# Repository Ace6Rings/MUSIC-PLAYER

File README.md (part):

# NOIR MUSIC PLAYER

# Why?

Why did I build something like this? Well, I am sick and tired of buying spotify premium every month. I looked for mp3 players online but nearly all of them have the same flaw(s). 
They either have a very short battery life or they don't support bluetooth. This would mean that my headphones will last three times as long as a typical mp3 player. So, I solved all of these problems with my own music player.

# Features

  - expandable storage via micro sd card
  - bluetooth range of ~100 meters in open air
  - Dual compatibility with both wired and wireless. 
  - High quality wired and wireless audio
  - Extremely high battery life (not tested)

## Electronics

So what about my electronics makes these features possible?

I use the NRF5430 <br>
  - The NRF5430 is a dual core chip that have the capability of being hyper efficient during its operation. <br>
  - Its power consumption is measured in the microamps during sleep mode and miliamps during full operation.

The PCM5102A and the TPA6132A2RTE <br>
  - the audio from common microcontrollers are low quality and unenjoyable for music. So I used the PCM5102A. It is a high quality DAC which will be wired to the TPA6132ARTE. <br>
  - the TPA6132ARTE increases the volume of the sound and also helps with the bass.<br>
  - with these two components, the wired quality should be no different (if not, better) than a phone or a typical mp3 player.

What about some safety features?

I have 2 layers of protection.

  According to my schematic, the battery and the usbc is tied to the same net. This means that they share the same electrical path.<br>
  To prevent any damage, I used mosfets which prevents both of them from turning on at the same time.<br>
  Additionally, I used the PRTR5V0U2X. It is a tvs diode which can prevent damage to the usbc and the board if something goes horribly wrong.

The rest of the electronics can be found in the electronics subdirectory. You can also find the production files there too. For the reviewer, make sure to read the mini readme in the electronics directory.

## Mechanical

The case of the music player is largely modeled after the Iphone 16 pro's dimensions. It is a reasonable size for a mp3 player and is also the reason why I can fit such a big battery.

There isn't any special about the case itself. This is designed for printers like the A1 mini, A1, and X1 Carbon with PLA basic.
If you took a look at my CAD already, you might be worried about how thin the wall is at the micro sd slot. So I ran some simulations.

I put a force of 20 newtons onto the faces of the socket and made the opposite wall a fixed support.
There could be more things you might want to see. You can do that under MECHANICAL and then click on simulations. <br>
NOTE: you need both the workbench file and also the zipped file too
CONTROL

This is the "before" part of the simulation.

And this is the after. 

Pretty much the same right? this means that my design is sound and could be used (as long as the user isn't a brute)

## Code
### MAKE SURE TO READ THE CORRESPONDING README INCLUDED IN THE CODE DIRECTORY TO ACTUALLY BUILD IT.
The backend of the code is built entirely by NORDIC, the company behind the NRF chips. I used their existing audio code so that I don't need to code my own (they have tens of thousands of lines of code)

The gui and function is limited because I have not recieved my pcb yet, and won't know what will happen if i implement something more than audio playback and some config files. This will change once I get my pcb.

Also note that the vast majority of the code is by NORDIC and their open source templates. All I did was make config files.

# Process

So what exactly is under the hood? Its a big schematic, so there is going to be 3 images.

## Schematic

As you can see, I'm using the NRF 5340 to power this project. Is there really much to say about this as of right now? Not really.

In this image, we can see that I'm using the TPA and PCM. These components work together to make wired audio great (hopefully). On the user side, you don't have to worry about this.
There is a headphone jack, and that is where you're going to plug in your headphones.

(yeah i don't know what to say about the schematic, I guess its cool?)

## PCB

If you've already opened the PCB file, then you might've been confused or bamboozled by how messy it is. But it really isn't!

This is what it is supposed to look like without user drawings (i used them to align things but never deleted them so I remember how much pain I went through).

Everything that needed to be said is already said in the features subtitle, but as an addendum, I added a cool snowman.

# How to use
Well how do you use it? I don't really know to be honest. The code is rudimentary and will be improved upon when I get my parts. As of right now, the controls are simple. The four buttons indicate direction, the center button indicates selection, and the rotary encoder is for volume up down and also a faster way to navigate the (future) gui.

# How to build

If you want to know how to build this physically, then heres a simple guide.

Thankfully, you don't need to do much at all! (assuming your pcb is already assembled. If not, good luck)

Just follow the steps in order!

1.Grab a soldering iron to put heat set inserts into the hole that label 1 is indicating. This is OPTIONAL, but you will need to adjust the cad to make it 2mm instead of 3mm.<br>
2.Screw in the screws as indicated in Label 1. There is only two holes but four mounts. Make sure to orientate it correctly! (the ports should line up with the case)<br>
3.Put the battery inside the two walls as indicated in label 2. Since everyone's printers are different, you will likely have to sand it. You can put double sided tape or velcro to secure the battery further, but otherwise, it should be fine. <br>
4.Put the ANO encoder into the cutout as indicated in Label 4.<br>
5.Put the cover onto the ANO encoder as indicated in Label 5.<br>
6.Screw it both in as indicated in Label 6.<br>
6.Use the JST compatible wires and connect them to the PCB.<br>
7.Do the same thing you just did to the ANO encoder in step 3. Instead, this time, you'll apply the same principle to the screen in Label 7, 8, and 9.<br>
NOTE: If you are unconfident in your soldering abilities, especially for the screen, you may adjust the "leeway" variable under "screen" folder and then the "mount" subfolder. The default is 2mm, do not go past 2.1mm. You may lower it if you want to, but the default should be ok. In addition, it is not reccomended to use the included pin headers for the screen, just solder the wire directly. The cover will hide any cosmetic issues.<br>

Hey! What about the battery? <br>
Well, since everyone can choose what lipo battery they will be using, I decided to make the battery area an open space. All you have to do is take a small piece of double sided tape (which many other commericial products do!) and tape the battery to the case. 

# BOM

NOTE: This file might be confusing. So heres some clarifications <br>

  - QTY refers to the actual amount needed. Amount refers to the amount bought due to minimum purchase limits. For assortment kits, qty is just 1.
  - Any item below the 45th row is not needed for this project (well they are). They are misc items that I don't have and I must put it down to get funding.
  - The NRF 5340 DK dev board is not needed, you only need a pico or etc to serve as an external programmer. I need this because I need to debug my code after I recieve my parts (so yes, again, this is for funding purposes)
  - shipping is done weirdly because I don't know how else to do it. However, you don't have to worry about that. There is a number on a seemingly random item that tells you the shipping price. Since alot of these items come from the same shop, the shipping is counted once. So items only have a shipping fee if it is the first on the list (by row) to have that specific shop.

And additionally, you might be thinking "woah, why is this so expensive?!" <br>
Well, most of the cost is actually the tools I need to program and assemble my project. You might already have these items!<br>

[tableConvert.com_6tsmnr.md](https://github.com/user-attachments/files/29273329/tableConvert.com_6tsmnr.md)
| Reference                                                                                 | Qty | Item                                                                                                          | DNP | Exclude from BOM | Exclude from Board  | Footprint                                                             | Datasheet                                                                                                                               | Link                                                                                                                                                                                                                                                                                                                                                                                                                                                                                                                                                                                                                                                                           | Amount | Cost  | SUBTOTAL | SHIPPING | TAXES     | TOTAL      |
|-------------------------------------------------------------------------------------------|-----|---------------------------------------------------------------------------------------------------------------|-----|------------------|---------------------|-----------------------------------------------------------------------|-----------------------------------------------------------------------------------------------------------------------------------------|--------------------------------------------------------------------------------------------------------------------------------------------------------------------------------------------------------------------------------------------------------------------------------------------------------------------------------------------------------------------------------------------------------------------------------------------------------------------------------------------------------------------------------------------------------------------------------------------------------------------------------------------------------------------------------|--------|-------|----------|----------|-----------|------------|
| C1,C4,C8,C10,C12,C24,C39,C40,C41,C43,C44,C45,C46,C50,C53                                  | 15  | 1u                                                                                                            |     |                  |                     | Capacitor_SMD:C_0402_1005Metric                                       |                                                                                                                                         | https://www.lcsc.com/product-detail/C29266.html?s_z=n_q_t_1uf%25200402&spm=wm.fly.bg.0.xh___wm.ssy.tc.0.tz&lcsc_vid=RFJeBVYFQQVeBV1XQwIMBQVQRlAPVVZeFlJcU1wHRwcxVlNeRlVXVF1VR1RaXjsOAxUeFF5JWBYZEEoKFBINSQcJGk4%3D                                                                                                                                                                                                                                                                                                                                                                                                                                                             | 100    | 0.53  | 209.2    | 7.27     | 21.724225 | 266.504225 |
| C2, C26, C47                                                                              | 3   | 2.2u                                                                                                          |     |                  |                     | Capacitor_SMD:C_0402_1005Metric                                       |                                                                                                                                         | https://www.lcsc.com/product-detail/C170151.html?s_z=n_q_t_2.2uf%25200402&spm=wm.fly.bg.0.xh___wm.ssy.tc.0.tz&lcsc_vid=RFJeBVYFQQVeBV1XQwIMBQVQRlAPVVZeFlJcU1wHRwcxVlNeRlVXVF1RRFNZXjsOAxUeFF5JWBYZEEoKFBINSQcJGk4NBhADEA4cHktXRlVcSQwSGg0%3D                                                                                                                                                                                                                                                                                                                                                                                                                                  | 50     | 0.5   |          |          |           |            |
| C3,C7,C15,C16,C17,C18,C19,C20,C21,C22,C23,C28,C29,C30,C31,C32,C33,C36,C38,C42,C48,C51,C52 | 23  | 100n                                                                                                          |     |                  |                     | Capacitor_SMD:C_0402_1005Metric                                       |                                                                                                                                         | https://www.lcsc.com/product-detail/C1525.html?s_z=n_q_t_100%2520nf%25200402&spm=wm.fly.bg.0.xh___wm.ssy.tc.0.tz&lcsc_vid=RFJeBVYFQQVeBV1XQwIMBQVQRlAPVVZeFlJcU1wHRwcxVlNeRlVXU1RQRlVbVjsOAxUeFF5JWBYZEEoKFBINSQcJGk4NBhADEA4cHktXRlVcSQwSGg0%3D                                                                                                                                                                                                                                                                                                                                                                                                                               | 100    | 0.23  |          |          |           |            |
| C5                                                                                        | 1   | 4.7u                                                                                                          | DNP |                  | Excluded from board | Capacitor_SMD:C_0603_1608Metric                                       |                                                                                                                                         |                                                                                                                                                                                                                                                                                                                                                                                                                                                                                                                                                                                                                                                                                |        |       |          |          |           |            |
| C6,C9,C11,C27                                                                             | 4   | 4.7u                                                                                                          |     |                  |                     | Capacitor_SMD:C_0603_1608Metric                                       |                                                                                                                                         | https://www.lcsc.com/product-detail/C19666.html?s_z=n_q_t_4.7uf&spm=wm.fly.bg.0.xh___wm.ssy.tc.1.tz&lcsc_vid=RFJeBVYFQQVeBV1XQwIMBQVQRlAPVVZeFlJcU1wHRwcxVlNeRlVXU1VSR1FWVTsOAxUeFF5JWBYZEEoKFBINSQcJGk4dAgUUFAk%3D                                                                                                                                                                                                                                                                                                                                                                                                                                                            | 10     | 0.22  |          |          |           |            |
| C13                                                                                       | 1   | 2.2n                                                                                                          |     |                  |                     | Capacitor_SMD:C_0402_1005Metric                                       |                                                                                                                                         | https://www.lcsc.com/product-detail/C107082.html?s_z=n_q_t_2.2nf&spm=wm.fly.bg.0.xh___wm.ssy.tc.0.tz&lcsc_vid=RFJeBVYFQQVeBV1XQwIMBQVQRlAPVVZeFlJcU1wHRwcxVlNeRlVXU1VfQlNWVDsOAxUeFF5JWBYZEEoKFBINSQcJGk4NBhADEA4cHktXRlVcSQwSGg0%3D                                                                                                                                                                                                                                                                                                                                                                                                                                           | 100    | 0.42  |          |          |           |            |
| C14                                                                                       | 1   | 0.7p                                                                                                          |     |                  |                     | Capacitor_SMD:C_0402_1005Metric                                       |                                                                                                                                         | https://www.lcsc.com/product-detail/C161349.html?s_z=n_q_t_0.7pf&spm=wm.fly.bg.0.xh___wm.ssy.tc.0.tz&lcsc_vid=RFJeBVYFQQVeBV1XQwIMBQVQRlAPVVZeFlJcU1wHRwcxVlNeRlVXU1ZSQFRaXzsOAxUeFF5JWBYZEEoKFBINSQcJGk4dAgUUFAk%3D                                                                                                                                                                                                                                                                                                                                                                                                                                                           | 50     | 0.83  |          |          |           |            |
| C37,C49                                                                                   | 2   | 10u                                                                                                           |     |                  |                     | Capacitor_SMD:C_0603_1608Metric                                       |                                                                                                                                         | https://www.lcsc.com/product-detail/C96446.html?s_z=n_q_t_10%2520uf&spm=wm.fly.bg.1.xh___wm.ssy.tc.1.tz&lcsc_vid=RFJeBVYFQQVeBV1XQwIMBQVQRlAPVVZeFlJcU1wHRwcxVlNeRlVXU1BRTlhbVTsOAxUeFF5JWBYZEEoKFBINSQcJGk4NBhADEA4cHktXRlVcSQwSGg0%3D                                                                                                                                                                                                                                                                                                                                                                                                                                        | 20     | 1.07  |          |          |           |            |
| C54                                                                                       | 1   | 10n                                                                                                           |     |                  |                     | Capacitor_SMD:C_0402_1005Metric                                       |                                                                                                                                         | https://www.lcsc.com/product-detail/C15195.html?s_z=n_q_t_10%2520nf&spm=wm.fly.bg.1.xh___wm.ssy.tc.0.tz&lcsc_vid=RFJeBVYFQQVeBV1XQwIMBQVQRlAPVVZeFlJcU1wHRwcxVlNeRlVXU1NST1BdVjsOAxUeFF5JWBYZEEoKFBINSQcJGk4NBhADEA4cHktXRlVcSQwSGg0%3D                                                                                                                                                                                                                                                                                                                                                                                                                                        | 100    | 0.25  |          |          |           |            |
| C55                                                                                       | 1   | NC                                                                                                            | DNP |                  |                     | Capacitor_SMD:C_0402_1005Metric                                       |                                                                                                                                         |                                                                                                                                                                                                                                                                                                                                                                                                                                                                                                                                                                                                                                                                                |        |       |          |          |           |            |
| D1, D3                                                                                    | 2   | POWER                                                                                                         |     |                  |                     | LED_SMD:LED_0603_1608Metric                                           |                                                                                                                                         | https://www.lcsc.com/product-detail/C19171394.html?s_z=n_q_t_led%25200603&spm=wm.fly.bg.0.xh___wm.ssy.tc.0.tz&lcsc_vid=RFJeBVYFQQVeBV1XQwIMBQVQRlAPVVZeFlJcU1wHRwcxVlNeRlVXU1xWQ1FYVzsOAxUeFF5JWBYZEEoKFBINSQcJGk4NBhADEA4cHktXRlVcSQwSGg0%3D                                                                                                                                                                                                                                                                                                                                                                                                                                  | 100    | 0.58  |          |          |           |            |
| D2                                                                                        | 1   | PRTR5V0U2X                                                                                                    |     |                  |                     | Package_TO_SOT_SMD:SOT-143                                            | https://assets.nexperia.com/documents/data-sheet/PRTR5V0U2X.pdf                                                                         | https://www.lcsc.com/product-detail/C2827688.html?s_z=n_q_PRTR5V0U2X&spm=wm.fly.bg.3.xh&lcsc_vid=RFJeBVYFQQVeBV1XQwIMBQVQRlAPVVZeFlJcU1wHRwcxVlNeRlVXUlRRT1JWVzsOAxUeFF5JWBYZEEoKFBINSQcJGk4eFQsCAgIaSgADAwAHC0slRlhfUFVVTlVADxALGw%3D%3D                                                                                                                                                                                                                                                                                                                                                                                                                                      | 10     | 0.61  |          |          |           |            |
| E1                                                                                        | 1   | 2450AT43B100E                                                                                                 |     |                  |                     | MyFootprintLibrary:ANTENNA_2450AT43B100E                              |                                                                                                                                         | https://www.lcsc.com/product-detail/C2917721.html?s_z=n_q_2450AT43B100E&spm=wm.fly.bg.0.xh&lcsc_vid=RFJeBVYFQQVeBV1XQwIMBQVQRlAPVVZeFlJcU1wHRwcxVlNeRlVXUldXQ1leUDsOAxUeFF5JWBYZEEoKFBINSQcJGk4NBhADEA4cHktRR1NADxALGw%3D%3D                                                                                                                                                                                                                                                                                                                                                                                                                                                   | 1      | 0.77  |          |          |           |            |
| FB1,FB2                                                                                   | 2   | TDK MPZ1608S221ATA00                                                                                          |     |                  |                     | myotherkicadfootprintlibrary:IND_1608_TDK                             |                                                                                                                                         | https://www.lcsc.com/product-detail/C76815.html?s_z=n_q_TDK%2520MPZ1608S221ATA00&spm=wm.fly.bg.0.xh&lcsc_vid=RFJeBVYFQQVeBV1XQwIMBQVQRlAPVVZeFlJcU1wHRwcxVlNeRlVXUldRQ1FaVzsOAxUeFF5JWBYZEEoKFBINSQcJGk4NBhADEA4cHktTQ1JADxALGw%3D%3D                                                                                                                                                                                                                                                                                                                                                                                                                                          | 10     | 0.15  |          |          |           |            |
| J1                                                                                        | 1   | USB_C_Receptacle_USB2.0_16P                                                                                   |     |                  |                     | Connector_USB:USB_C_Receptacle_GCT_USB4105-xx-A_16P_TopMnt_Horizontal | https://www.usb.org/sites/default/files/documents/usb_type-c.zip                                                                        | https://www.lcsc.com/product-image/C5184243.html?whichImg=pcb&lcsc_vid=ElQMUFdRTlJfX10FElUKBgVfTlhWUgJXRVMIUFZVE1QxVlNRT1JWVFReRFRbVTsOAxUeFF5JWBYZEEoKFBINSQcJGk4eFQsCAgIaSgADAwAHC0slRFFcV1FQR08GEwkK&spm=wm.sxq.inf.pcb.ltp___wm.fly.bg.1.xh                                                                                                                                                                                                                                                                                                                                                                                                                                | 1      | 0.97  |          |          |           |            |
| J2                                                                                        | 1   | JST CONNECTOR 1X3                                                                                             |     |                  |                     | Connector_JST:JST_PH_S3B-PH-K_1x03_P2.00mm_Horizontal                 |                                                                                                                                         | https://www.lcsc.com/product-detail/C157929.html?s_z=n_q_S3B-PH-K-S%28LF%29%28SN%29&spm=wm.fly.bg.0.xh&lcsc_vid=RFJeBVYFQQVeBV1XQwIMBQVQRlAPVVZeFlJcU1wHRwcxVlNeRlVXUlFVT1ZcUzsOAxUeFF5JWBYZEEoKFBINSQcJGk4dAgUUFAk%3D                                                                                                                                                                                                                                                                                                                                                                                                                                                         | 10     | 0.49  |          |          |           |            |
| J3                                                                                        | 1   | JST CONNECTOR 1X2                                                                                             |     |                  |                     | Connector_JST:JST_PH_S2B-PH-K_1x02_P2.00mm_Horizontal                 |                                                                                                                                         | https://www.lcsc.com/product-detail/C173752.html?s_z=n_q_S2B-PH-K-S%28LF%29%28SN%29&spm=wm.fly.bg.0.xh&lcsc_vid=RFJeBVYFQQVeBV1XQwIMBQVQRlAPVVZeFlJcU1wHRwcxVlNeRlVXUlFRTlFXVzsOAxUeFF5JWBYZEEoKFBINSQcJGk4NBhADEA4cHktRTlNADxALGw%3D%3D                                                                                                                                                                                                                                                                                                                                                                                                                                       | 20     | 0.79  |          |          |           |            |
| J4                                                                                        | 1   | MSD-4-A                                                                                                       |     |                  |                     | MyFootprintLibrary:CUI_MSD-4-A                                        |                                                                                                                                         | https://www.lcsc.com/product-detail/C22367949.html?s_z=n_q_msd-4-a&spm=wm.fly.bg.0.xh&lcsc_vid=RFJeBVYFQQVeBV1XQwIMBQVQRlAPVVZeFlJcU1wHRwcxVlNeRlVXUlJWQFlZVDsOAxUeFF5JWBYZEEoKFBINSQcJGk4eFQsCAgIaSgADAwAHC0slRlZdUFFUWQkaCgg%3D                                                                                                                                                                                                                                                                                                                                                                                                                                              | 1      | 0.83  |          |          |           |            |
| J5                                                                                        | 1   | SJ-43514                                                                                                      |     |                  |                     | MyFootprintLibrary:CUI_SJ-43514                                       |                                                                                                                                         | https://www.digikey.com/en/products/detail/same-sky-formerly-cui-devices/SJ-43514/368146                                                                                                                                                                                                                                                                                                                                                                                                                                                                                                                                                                                       | 1      | 1.34  |          |          |           |            |
| L1, L2, L3                                                                                | 3   | 10uH                                                                                                          |     |                  |                     | Inductor_SMD:L_0402_1005Metric                                        |                                                                                                                                         | https://www.lcsc.com/product-detail/C910650.html?s_z=n_q_10uh%25200402&spm=wm.fly.bg.0.xh&lcsc_vid=RFJeBVYFQQVeBV1XQwIMBQVQRlAPVVZeFlJcU1wHRwcxVlNeRlVXUVZRR1lYUTsOAxUeFF5JWBYZEEoKFBINSQcJGk4NBhADEA4cHktXRllfSQwSGg0%3D                                                                                                                                                                                                                                                                                                                                                                                                                                                      | 5      | 3.01  |          |          |           |            |
| L4                                                                                        | 1   | 2.2n                                                                                                          |     |                  |                     | Inductor_SMD:L_0402_1005Metric                                        |                                                                                                                                         | https://www.lcsc.com/product-detail/C91240.html?s_z=n_q_2.2nh%25200402&spm=wm.fly.bg.0.xh&lcsc_vid=RFJeBVYFQQVeBV1XQwIMBQVQRlAPVVZeFlJcU1wHRwcxVlNeRlVXUVdUQ1RfVzsOAxUeFF5JWBYZEEoKFBINSQcJGk4dAgUUFAk%3D                                                                                                                                                                                                                                                                                                                                                                                                                                                                      | 10     | 0.5   |          |          |           |            |
| Q1,Q2                                                                                     | 2   | DMG2301L                                                                                                      |     |                  |                     | Package_TO_SOT_SMD:SOT-23                                             | https://www.diodes.com/assets/Datasheets/DMG2301L.pdf                                                                                   | https://www.lcsc.com/product-detail/C7472914.html?s_z=n_q_DMG2301L&spm=wm.fly.bg.0.xh&lcsc_vid=RFJeBVYFQQVeBV1XQwIMBQVQRlAPVVZeFlJcU1wHRwcxVlNeRlVXUVdTTlVYUTsOAxUeFF5JWBYZEEoKFBINSQcJGk4NBhADEA4cHktXRllfSQwSGg0%3D                                                                                                                                                                                                                                                                                                                                                                                                                                                          | 10     | 0.58  |          |          |           |            |
| R1,R2                                                                                     | 2   | 5.1K                                                                                                          |     |                  |                     | Resistor_SMD:R_0402_1005Metric                                        |                                                                                                                                         | https://www.lcsc.com/product-detail/C852856.html?s_z=n_q_t_5.1k%25200402&spm=wm.fly.bg.0.xh___wm.ssy.tc.0.tz&lcsc_vid=RFJeBVYFQQVeBV1XQwIMBQVQRlAPVVZeFlJcU1wHRwcxVlNeRlVXUVBRR1daUDsOAxUeFF5JWBYZEEoKFBINSQcJGk4NBhADEA4cHktXRlhXSQwSGg0%3D                                                                                                                                                                                                                                                                                                                                                                                                                                   | 50     | 1.08  |          |          |           |            |
| R3, R13, R14                                                                              | 3   | 10k                                                                                                           |     |                  |                     | Resistor_SMD:R_0402_1005Metric                                        |                                                                                                                                         | https://www.lcsc.com/product-detail/C190095.html?s_z=n_q_t_10k%25200402&spm=wm.fly.bg.1.xh___wm.ssy.tc.0.tz&lcsc_vid=RFJeBVYFQQVeBV1XQwIMBQVQRlAPVVZeFlJcU1wHRwcxVlNeRlVXUVFVQFNXXzsOAxUeFF5JWBYZEEoKFBINSQcJGk4NBhADEA4cHktXRlhXSQwSGg0%3D                                                                                                                                                                                                                                                                                                                                                                                                                                    | 50     | 0.93  |          |          |           |            |
| R4                                                                                        | 1   | 2R2                                                                                                           |     |                  |                     | Resistor_SMD:R_0402_1005Metric                                        |                                                                                                                                         | https://www.lcsc.com/product-detail/C3013277.html?s_z=n_q_t_2r2%2520&spm=wm.fly.bg.0.xh___wm.ssy.tc.0.tz&lcsc_vid=RFJeBVYFQQVeBV1XQwIMBQVQRlAPVVZeFlJcU1wHRwcxVlNeRlVXUVJUT1ZYVjsOAxUeFF5JWBYZEEoKFBINSQcJGk4NBhADEA4cHktXRlhXSQwSGg0%3D                                                                                                                                                                                                                                                                                                                                                                                                                                       | 50     | 0.64  |          |          |           |            |
| R5                                                                                        | 1   | 100                                                                                                           |     |                  |                     | Resistor_SMD:R_0402_1005Metric                                        |                                                                                                                                         | https://www.lcsc.com/product-detail/C106232.html?s_z=n_q_t_100%25CE%25A9%25200402&spm=wm.fly.bg.0.xh___wm.ssy.tc.0.tz&lcsc_vid=RFJeBVYFQQVeBV1XQwIMBQVQRlAPVVZeFlJcU1wHRwcxVlNeRlVXUVNWQ1ddVTsOAxUeFF5JWBYZEEoKFBINSQcJGk4dAgUUFAk%3D                                                                                                                                                                                                                                                                                                                                                                                                                                          | 100    | 0.1   |          |          |           |            |
| R6                                                                                        | 1   | 1k                                                                                                            |     |                  |                     | Resistor_SMD:R_0402_1005Metric                                        |                                                                                                                                         | https://www.lcsc.com/product-detail/C852624.html?s_z=n_q_t_1k%25200402&spm=wm.fly.bg.0.xh___wm.ssy.tc.0.tz&lcsc_vid=RFJeBVYFQQVeBV1XQwIMBQVQRlAPVVZeFlJcU1wHRwcxVlNeRlVXUVNSQVVYXzsOAxUeFF5JWBYZEEoKFBINSQcJGk4NBhADEA4cHktXRlhXSQwSGg0%3D                                                                                                                                                                                                                                                                                                                                                                                                                                     | 50     | 0.89  |          |          |           |            |
| R7                                                                                        | 1   | 2.2k                                                                                                          |     |                  |                     | Resistor_SMD:R_0402_1005Metric                                        |                                                                                                                                         | https://www.lcsc.com/product-detail/C2906920.html?s_z=n_q_t_2.2k%25200402&spm=wm.fly.bg.0.xh___wm.ssy.tc.0.tz&lcsc_vid=RFJeBVYFQQVeBV1XQwIMBQVQRlAPVVZeFlJcU1wHRwcxVlNeRlVXUVNRQVZeVzsOAxUeFF5JWBYZEEoKFBINSQcJGk4NBhADEA4cHktXRlhXSQwSGg0%3D                                                                                                                                                                                                                                                                                                                                                                                                                                  | 100    | 0.1   |          |          |           |            |
| R8,R9                                                                                     | 2   | 1M                                                                                                            |     |                  |                     | Resistor_SMD:R_0402_1005Metric                                        |                                                                                                                                         | https://www.lcsc.com/product-detail/C2929915.html?s_z=n_q_2m%25200402&spm=wm.fly.bg.1.xh&lcsc_vid=RFJeBVYFQQVeBV1XQwIMBQVQRlAPVVZeFlJcU1wHRwcxVlNeRlVXUVxWRVVfVTsOAxUeFF5JWBYZEEoKFBINSQcJGk4NBhADEA4cHktXRlhXSQwSGg0%3D                                                                                                                                                                                                                                                                                                                                                                                                                                                       | 100    | 0.1   |          |          |           |            |
| R10                                                                                       | 1   | 2k                                                                                                            |     |                  |                     | Resistor_SMD:R_0402_1005Metric                                        |                                                                                                                                         | https://www.lcsc.com/product-detail/C2906921.html?s_z=n_q_t_2k%25200402&spm=wm.fly.bg.0.xh___wm.ssy.tc.0.tz&lcsc_vid=RFJeBVYFQQVeBV1XQwIMBQVQRlAPVVZeFlJcU1wHRwcxVlNeRlVXUVxVR1ZXUTsOAxUeFF5JWBYZEEoKFBINSQcJGk4NBhADEA4cHktXRlhXSQwSGg0%3D                                                                                                                                                                                                                                                                                                                                                                                                                                    | 100    | 0.09  |          |          |           |            |
| R11                                                                                       | 1   | 22k                                                                                                           |     |                  |                     | Resistor_SMD:R_0402_1005Metric                                        |                                                                                                                                         | https://www.lcsc.com/product-detail/C82868.html?s_z=n_q_t_22k%25200402&spm=wm.fly.bg.0.xh___wm.ssy.tc.0.tz&lcsc_vid=RFJeBVYFQQVeBV1XQwIMBQVQRlAPVVZeFlJcU1wHRwcxVlNeRlVXUVxTQlNYVTsOAxUeFF5JWBYZEEoKFBINSQcJGk4NBhADEA4cHktXRlhXSQwSGg0%3D                                                                                                                                                                                                                                                                                                                                                                                                                                     | 100    | 0.1   |          |          |           |            |
| R12                                                                                       | 1   | 470                                                                                                           |     |                  |                     | Resistor_SMD:R_0402_1005Metric                                        |                                                                                                                                         | https://www.lcsc.com/product-detail/C2909361.html?s_z=n_q_t_470%25CE%25A9%25200402&spm=wm.fly.bg.0.xh___wm.ssy.tc.0.tz&lcsc_vid=RFJeBVYFQQVeBV1XQwIMBQVQRlAPVVZeFlJcU1wHRwcxVlNeRlVXUV1VTllfVjsOAxUeFF5JWBYZEEoKFBINSQcJGk4NBhADEA4cHktXRlhXSQwSGg0%3D                                                                                                                                                                                                                                                                                                                                                                                                                         | 100    | 0.1   |          |          |           |            |
| R15                                                                                       | 1   | 4.7k                                                                                                          |     |                  |                     | Resistor_SMD:R_0402_1005Metric                                        |                                                                                                                                         | https://www.lcsc.com/product-detail/C42396697.html?s_z=n_q_t_4.70%25CE%25A9%25200402&spm=wm.fly.bg.0.xh___wm.ssy.tc.0.tz&lcsc_vid=RFJeBVYFQQVeBV1XQwIMBQVQRlAPVVZeFlJcU1wHRwcxVlNeRlVXUFRWRlJWXzsOAxUeFF5JWBYZEEoKFBINSQcJGk4NBhADEA4cHktXRlhXSQwSGg0%3D                                                                                                                                                                                                                                                                                                                                                                                                                       | 100    | 0.22  |          |          |           |            |
| SW1                                                                                       | 1   | B3U-1000P                                                                                                     |     |                  |                     | myotherkicadfootprintlibrary:B3U-1000P                                |                                                                                                                                         | https://www.lcsc.com/product-detail/C231329.html?s_z=n_q_B3U-1000P&spm=wm.fly.bg.0.xh&lcsc_vid=RFJeBVYFQQVeBV1XQwIMBQVQRlAPVVZeFlJcU1wHRwcxVlNeRlVXUFReRlNYVjsOAxUeFF5JWBYZEEoKFBINSQcJGk4NBhADEA4cHktXRlhXSQwSGg0%3D                                                                                                                                                                                                                                                                                                                                                                                                                                                          | 5      | 0.89  |          |          |           |            |
| U1                                                                                        | 1   |                                                                                                               |     |                  |                     | Connector_JST:JST_PH_S9B-PH-K_1x09_P2.00mm_Horizontal                 |                                                                                                                                         | https://www.lcsc.com/product-detail/C157912.html?s_z=n_q_S9B-PH-K-S&spm=wm.fly.bg.0.xh&lcsc_vid=RFJeBVYFQQVeBV1XQwIMBQVQRlAPVVZeFlJcU1wHRwcxVlNeRlVXUFVSQ1BdUzsOAxUeFF5JWBYZEEoKFBINSQcJGk4NBhADEA4cHktQQlBADxALGw%3D%3D                                                                                                                                                                                                                                                                                                                                                                                                                                                       | 5      | 0.92  |          |          |           |            |
| U2                                                                                        | 1   | nRF5340-QKAA-R                                                                                                |     |                  |                     | Package_DFN_QFN:Nordic_AQFN-94-1EP_7x7mm_P0.4mm                       | https://infocenter.nordicsemi.com/pdf/nRF5340_PS_v1.2.pdf                                                                               | https://www.lcsc.com/product-detail/C3015611.html?s_z=n_q_nrf%25205340%2520qkaa&spm=wm.fly.bg.1.xh&lcsc_vid=RFJeBVYFQQVeBV1XQwIMBQVQRlAPVVZeFlJcU1wHRwcxVlNeRlVXUFVeRFZbUTsOAxUeFF5JWBYZEEoKFBINSQcJGk4dAgUUFAk%3Dhttps://www.lcsc.com/product-detail/C3015611.html?s_z=n_q_nrf%25205340%2520qkaa&spm=wm.fly.bg.1.xh&lcsc_vid=RFJeBVYFQQVeBV1XQwIMBQVQRlAPVVZeFlJcU1wHRwcxVlNeRlVXUFVeRFZbUTsOAxUeFF5JWBYZEEoKFBINSQcJGk4dAgUUFAk%3D                                                                                                                                                                                                                                           | 1      | 7.59  |          |          |           |            |
| U3                                                                                        | 1   | SPX3819M5-L-3-3                                                                                               |     |                  |                     | Package_TO_SOT_SMD:SOT-23-5                                           | https://www.exar.com/content/document.ashx?id=22106&languageid=1033&type=Datasheet&partnumber=SPX3819&filename=SPX3819.pdf&part=SPX3819 | https://www.lcsc.com/product-detail/C9055.html?s_z=n_q_SPX3819M5-L-3-3&spm=wm.fly.bg.0.xh&lcsc_vid=RFJeBVYFQQVeBV1XQwIMBQVQRlAPVVZeFlJcU1wHRwcxVlNeRlVXUFZUTlBZXzsOAxUeFF5JWBYZEEoKFBINSQcJGk4eFQsCAgIaSgADAwAHC0slRFFfUlJXRk8GEwkK                                                                                                                                                                                                                                                                                                                                                                                                                                            | 10     | 1.78  |          |          |           |            |
| U4                                                                                        | 1   |                                                                                                               |     |                  |                     | Connector_JST:JST_PH_S8B-PH-K_1x08_P2.00mm_Horizontal                 |                                                                                                                                         | https://www.lcsc.com/product-detail/C157915.html?s_z=n_q_JST%2520S8B-PH-K-S%28LF%29%28SN%29&spm=wm.fly.bg.0.xh&lcsc_vid=RFJeBVYFQQVeBV1XQwIMBQVQRlAPVVZeFlJcU1wHRwcxVlNeRlVXUFZQT1VaUzsOAxUeFF5JWBYZEEoKFBINSQcJGk4eFQsCAgIaSgADAwAHC0slRlRZXlVUWQkaCgg%3D                                                                                                                                                                                                                                                                                                                                                                                                                     | 5      | 0.54  |          |          |           |            |
| U5                                                                                        | 1   | MCP73831-2-OT                                                                                                 |     |                  |                     | Package_TO_SOT_SMD:SOT-23-5                                           | http://ww1.microchip.com/downloads/en/DeviceDoc/20001984g.pdf                                                                           | https://www.lcsc.com/product-detail/C424093.html?s_z=s_p_x_MCP73831T-2ACI%252FOT&spm=wm.ssy.em.0.tz&lcsc_vid=RFJeBVYFQQVeBV1XQwIMBQVQRlAPVVZeFlJcU1wHRwcxVlNeRlVXUFdSQVJZXjsOAxUeFF5JWBYZEEoKFBINSQcJGk4NBhADEA4cHktXR1FaSQwSGg0%3D                                                                                                                                                                                                                                                                                                                                                                                                                                            | 1      | 0.81  |          |          |           |            |
| U6                                                                                        | 1   | TPA6132A2RTE                                                                                                  |     |                  |                     | Package_DFN_QFN:WQFN-16-1EP_3x3mm_P0.5mm_EP1.6x1.6mm_ThermalVias      | https://www.ti.com/lit/ds/symlink/tpa6132a2.pdf                                                                                         | https://www.lcsc.com/product-detail/C69901.html?s_z=n_q_TPA6132A2RTE&spm=wm.fly.bg.0.xh&lcsc_vid=RFJeBVYFQQVeBV1XQwIMBQVQRlAPVVZeFlJcU1wHRwcxVlNeRlVXUFdeQ1JYUDsOAxUeFF5JWBYZEEoKFBINSQcJGk4eFQsCAgIaSgADAwAHC0slQ1NaV11VWQkaCgg%3D                                                                                                                                                                                                                                                                                                                                                                                                                                            | 1      | 1.31  |          |          |           |            |
| U7                                                                                        | 1   | PCM5102A                                                                                                      |     |                  |                     | Package_SO:TSSOP-20_4.4x6.5mm_P0.65mm                                 | http://www.ti.com/lit/ds/symlink/pcm5100.pdf                                                                                            | https://www.lcsc.com/product-detail/C107671.html?s_z=n_q_%2520PCM5102A&spm=wm.fly.bg.1.xh&lcsc_vid=RFJeBVYFQQVeBV1XQwIMBQVQRlAPVVZeFlJcU1wHRwcxVlNeRlVXUFBUQFVbUjsOAxUeFF5JWBYZEEoKFBINSQcJGk4NBhADEA4cHktXQ1BbSQwSGg0%3D                                                                                                                                                                                                                                                                                                                                                                                                                                                      | 1      | 1.11  |          |          |           |            |
| Y1                                                                                        | 1   | Seiko SC-20S                                                                                                  |     |                  |                     | Crystal:Crystal_SMD_2012-2Pin_2.0x1.2mm                               |                                                                                                                                         | https://www.digikey.com/en/products/detail/seiko-instruments/SC20S-7PF20PPM/4931506                                                                                                                                                                                                                                                                                                                                                                                                                                                                                                                                                                                            | 1      | 0.72  |          | 8.49     |           |            |
| Y2                                                                                        | 1   | NX2016SA-CS06654                                                                                              |     |                  |                     | myotherkicadfootprintlibrary:NX2016SA_NDK                             |                                                                                                                                         | https://www.lcsc.com/product-detail/C5441424.html?s_z=n_q_p_NX2016SA-CS06654&spm=wm.ssy.bg.0.xh&lcsc_vid=RFJeBVYFQQVeBV1XQwIMBQVQRlAPVVZeFlJcU1wHRwcxVlNeRlVXUFJQQFhWVzsOAxUeFF5JWBYZEEoKFBINSQcJGk4eFQsCAgIaSgADAwAHC0slQVhXV1VIHxUDCw%3D%3D                                                                                                                                                                                                                                                                                                                                                                                                                                  | 1      | 0.44  |          |          |           |            |
|                                                                                           |     | NRF 5340 DK                                                                                                   |     |                  |                     |                                                                       |                                                                                                                                         | "                                                                                                                                                                                                                                                                                                                                                                                                                                                                                                                                                                                                                                                                              |        |       |          |          |           |            |
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
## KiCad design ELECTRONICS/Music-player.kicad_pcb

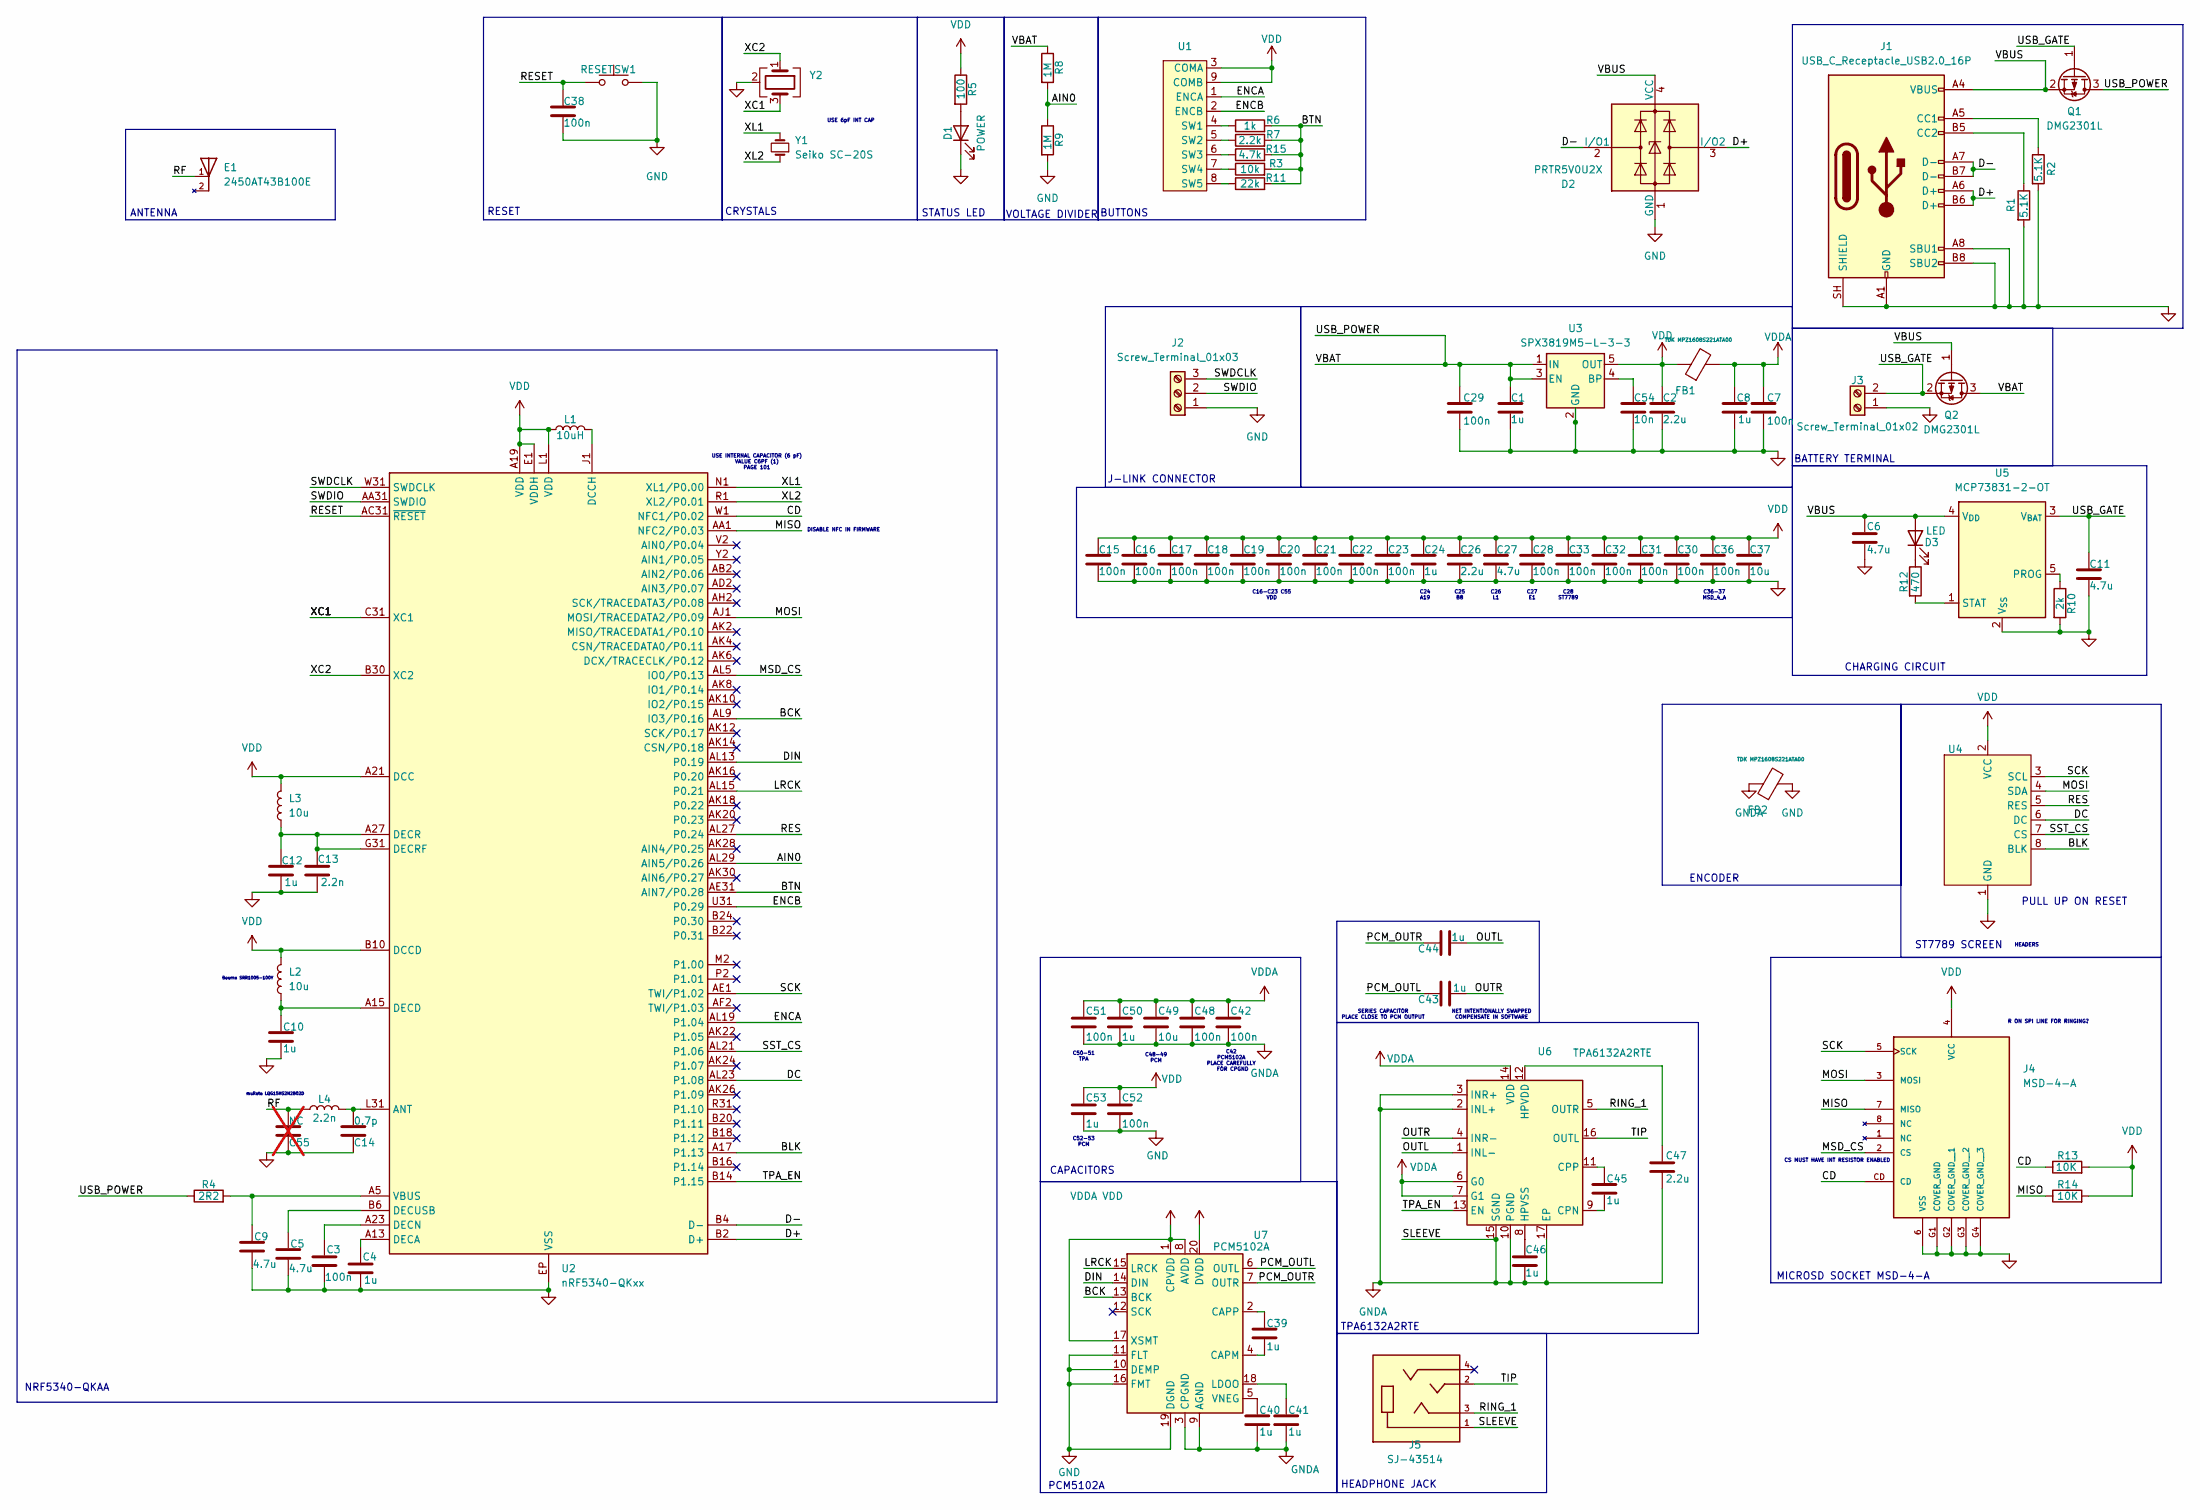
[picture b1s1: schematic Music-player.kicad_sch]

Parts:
C1, C4, C8, C10, C12, C24, C39, C40, C41, C43, C44, C45, C46, C50, C53: 1u; C_0402_1005Metric
C2, C26, C47: 2.2u; C_0402_1005Metric
C3, C7, C15, C16, C17, C18, C19, C20, C21, C22, C23, C28, C29, C30, C31, C32, C33, C36, C38, C42, C48, C51, C52: 100n; C_0402_1005Metric
C5, C6, C9, C11, C27: 4.7u; C_0603_1608Metric
C13: 2.2n; C_0402_1005Metric
C14: 0.7p; C_0402_1005Metric
C37, C49: 10u; C_0603_1608Metric
C54: 10n; C_0402_1005Metric
C55: NC; C_0402_1005Metric; not fitted
D1: POWER; LED_0603_1608Metric
D2: PRTR5V0U2X; SOT-143
D3: LED; LED_0603_1608Metric
E1: 2450AT43B100E; ANTENNA_2450AT43B100E; PARTREV 4.0
FB1, FB2: TDK MPZ1608S221ATA00; IND_1608_TDK
J1: USB_C_Receptacle_USB2.0_16P; USB_C_Receptacle_GCT_USB4105-xx-A_16P_TopMnt_Horizontal
J2: Screw_Terminal_01x03; JST_PH_S3B-PH-K_1x03_P2.00mm_Horizontal
J3: Screw_Terminal_01x02; JST_PH_S2B-PH-K_1x02_P2.00mm_Horizontal
J4: MSD-4-A; CUI_MSD-4-A; PARTREV 1.0
J5: SJ-43514; CUI_SJ-43514; PART_REV 1.04
L1: 10uH; L_0402_1005Metric
L2, L3: 10u; L_0402_1005Metric
L4: 2.2n; L_0402_1005Metric
Q1, Q2: DMG2301L; SOT-23
R1, R2: 5.1K; R_0402_1005Metric
R3: 10k; R_0402_1005Metric
R4: 2R2; R_0402_1005Metric
R5: 100; R_0402_1005Metric
R6: 1k; R_0402_1005Metric
R7: 2.2k; R_0402_1005Metric
R8, R9: 1M; R_0402_1005Metric
R10: 2k; R_0402_1005Metric
R11: 22k; R_0402_1005Metric
R12: 470; R_0402_1005Metric
R13, R14: 10K; R_0402_1005Metric
R15: 4.7k; R_0402_1005Metric
SW1: RESET; B3U-1000P
U1: JST_PH_S9B-PH-K_1x09_P2.00mm_Horizontal
U2: nRF5340-QKxx; Nordic_AQFN-94-1EP_7x7mm_P0.4mm
U3: SPX3819M5-L-3-3; SOT-23-5
U4: JST_PH_S8B-PH-K_1x08_P2.00mm_Horizontal
U5: MCP73831-2-OT; SOT-23-5
U6: TPA6132A2RTE; WQFN-16-1EP_3x3mm_P0.5mm_EP1.6x1.6mm_ThermalVias
U7: PCM5102A; TSSOP-20_4.4x6.5mm_P0.65mm
Y1: Seiko SC-20S; Crystal_SMD_2012-2Pin_2.0x1.2mm
Y2: NX2016SA-CS06654; NX2016SA_NDK

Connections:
/AIN0: R8.2, R9.1, U2.AL29 (AIN5/P0.26)
/BCK: U2.AL9 (IO3/P0.16), U7.13 (BCK)
/BLK: U2.A17 (P1.13), U4.8 (BLK)
/BTN: R3.2, R6.2, R7.2, R11.2, R15.2, U2.AE31 (AIN7/P0.28)
/CD: J4.CD, R13.1, U2.W1 (NFC1/P0.02)
/D+: D2.3 (I/O2), J1.A6 (D+), J1.B6 (D+), U2.B2 (D+)
/D-: D2.2 (I/O1), J1.A7 (D-), J1.B7 (D-), U2.B4 (D-)
/DC: U2.AL23 (P1.08), U4.6 (DC)
/DIN: U2.AL13 (P0.19), U7.14 (DIN)
/ENCA: U1.1 (ENCA), U2.AL19 (P1.04)
/ENCB: U1.2 (ENCB), U2.U31 (P0.29)
/LRCK: U2.AL15 (P0.21), U7.15 (LRCK)
/MISO: J4.7 (MISO), R14.1, U2.AA1 (NFC2/P0.03)
/MOSI: J4.3 (MOSI), U2.AJ1 (MOSI/TRACEDATA2/P0.09), U4.4 (SDA)
/MSD_CS: J4.2 (CS), U2.AL5 (IO0/P0.13)
/OUTL: C44.2, U6.1 (INL-)
/OUTR: C43.2, U6.4 (INR-)
/PCM_OUTL: C43.1, U7.6 (OUTL)
/PCM_OUTR: C44.1, U7.7 (OUTR)
/RES: U2.AL27 (P0.24), U4.5 (RES)
/RESET: C38.1, SW1.1, U2.AC31 (~RESET)
/RF: C55.1, E1.1, L4.1
/RING_1: J5.3, U6.5 (OUTR)
/SCK: J4.5 (SCK), U2.AE1 (TWI/P1.02), U4.3 (SCL)
/SST_CS: U2.AL21 (P1.06), U4.7 (CS)
/SWDCLK: J2.3, U2.W31 (SWDCLK)
/SWDIO: J2.2, U2.AA31 (SWDIO)
/TIP: J5.2, U6.16 (OUTL)
/TPA_EN: U2.B14 (P1.15), U6.13 (EN)
/USB_GATE: C11.1, J3.2, Q1.1 (G), Q2.2 (S), U5.3 (V_{BAT})
/USB_POWER: C1.1, C29.1, Q1.3 (D), Q2.3 (D), R4.1, R8.1, U3.1 (IN), U3.3 (EN)
/VBUS: C6.1, D2.4 (VCC), D3.2 (A), J1.A4 (VBUS), J1.A9 (VBUS), J1.B4 (VBUS), J1.B9 (VBUS), Q1.2 (S), Q2.1 (G), U5.4 (V_{DD})
/XC1: U2.C31 (XC1), Y2.3
/XC2: U2.B30 (XC2), Y2.1
/XL1: U2.N1 (XL1/P0.00), Y1.2
/XL2: U2.R1 (XL2/P0.01), Y1.1
GND: C1.2, C2.2, C3.2, C4.2, C5.2, C6.2, C7.2, C8.2, C9.2, C10.2, C11.2, C12.2, C13.2, C14.2, C15.2, C16.2, C17.2, C18.2, C19.2, C20.2, C21.2, C22.2, C23.2, C24.2, C26.2, C27.2, C28.2, C29.2, C30.2, C31.2, C32.2, C33.2, C36.2, C37.2, C38.2, C52.2, C53.2, C54.2, C55.2, D1.1 (K), D2.1 (GND), FB2.2, J1.A1 (GND), J1.A8 (SBU1), J1.A12 (GND), J1.B1 (GND), J1.B8 (SBU2), J1.B12 (GND), J1.SH (SHIELD), J2.1, J3.1, J4.6 (VSS), J4.G1 (COVER_GND), J4.G2 (COVER_GND__1), J4.G3 (COVER_GND__2), J4.G4 (COVER_GND__3), R1.2, R2.2, R9.2, R10.2, SW1.2, U2.EP (VSS), U3.2 (GND), U4.1 (GND), U5.2 (V_{SS}), U7.10 (DEMP), U7.11 (FLT), U7.16 (FMT), U7.19 (DGND), Y2.2 (G), Y2.4 (G); also elsewhere on the board
GNDA: C40.2, C41.2, C42.2, C46.2, C47.2, C48.2, C49.2, C50.2, C51.2, FB2.1, J5.1, U6.2 (INL+), U6.3 (INR+), U6.10 (PGND), U6.15 (SGND), U6.17 (EP), U7.3 (CPGND), U7.9 (AGND)
unnamed: D1.2 (A), R5.2
unnamed: D3.1 (K), R12.1
unnamed: J1.A5 (CC1), R2.1
unnamed: J1.B5 (CC2), R1.1
unnamed: R6.1, U1.4 (SW1)
unnamed: R7.1, U1.5 (SW2)
unnamed: R15.1, U1.6 (SW3)
unnamed: R3.1, U1.7 (SW4)
unnamed: R11.1, U1.8 (SW5)
unnamed: C14.1, L4.2, U2.L31 (ANT)
unnamed: L1.2, U2.J1 (DCCH)
unnamed: C4.1, U2.A13 (DECA)
unnamed: C10.1, L2.1, U2.A15 (DECD)
unnamed: C3.1, U2.A23 (DECN)
unnamed: C12.1, C13.1, L3.1, U2.A27 (DECR), U2.G31 (DECRF)
unnamed: C54.1, U3.4 (BP)
unnamed: R10.1, U5.5 (PROG)
unnamed: R12.2, U5.1 (STAT)
unnamed: C45.2, U6.9 (CPN)
unnamed: C45.1, U6.11 (CPP)
unnamed: C47.1, U6.12 (HPVDD)
unnamed: C46.1, U6.8 (HPVSS)
unnamed: C39.2, U7.4 (CAPM)
unnamed: C39.1, U7.2 (CAPP)
unnamed: C41.1, U7.18 (LDOO)
unnamed: C40.1, U7.5 (VNEG)
VDD: C2.1, C15.1, C16.1, C17.1, C18.1, C19.1, C20.1, C21.1, C22.1, C23.1, C24.1, C26.1, C27.1, C28.1, C30.1, C31.1, C32.1, C33.1, C36.1, C37.1, C52.1, C53.1, FB1.1, J4.4 (VCC), L1.1, L2.2, L3.2, R5.1, R13.2, R14.2, U1.3 (COMA), U1.9 (COMB), U2.A19 (VDD), U2.A21 (DCC), U2.AC1 (VDD), U2.AG1 (VDD), U2.AJ31 (VDD), U2.AL3 (VDD), U2.AL7 (VDD), U2.AL11 (VDD), U2.AL17 (VDD), U2.AL25 (VDD), U2.B8 (VDD), U2.B10 (DCCD), U2.B28 (VDD), U2.C1 (VDD), U2.E1 (VDDH), U2.E31 (VDD), U2.L1 (VDD), U2.N31 (VDD), U2.U1 (VDD), U3.5 (OUT), U4.2 (VCC), U7.20 (DVDD)
VDDA: C7.1, C8.1, C42.1, C48.1, C49.1, C50.1, C51.1, FB1.2, U6.6 (G0), U6.7 (G1), U6.14 (VDD), U7.1 (CPVDD), U7.8 (AVDD), U7.17 (XSMT)

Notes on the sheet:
C26 L1
SERIES CAPACITOR PLACE CLOSE TO PCM OUTPUT
CS MUST HAVE INT RESISTOR ENABLED
C50-51 TPA
C36-37 MSD_4_A
C28 ST7789
ST7789 SCREEN
VOLTAGE DIVIDER
C24 A19
PULL UP ON RESET
CRYSTALS
CHARGING CIRCUIT
CAPACITORS
MICROSD SOCKET MSD-4-A
STATUS LED
NRF5340-QKAA
USE 6pF INT CAP
C52-53 PCM
C48-49 PCM
RESET
R ON SPI LINE FOR RINGING?
C42 PCM5102A PLACE CAREFULLY FOR CPGND
USE INTERNAL CAPACITOR (6 pF) VALUE C6PF (1) PAGE 101
C16-C23 C55 VDD
C25 B8
TPA6132A2RTE
NET INTENTIONALLY SWAPPED COMPENSATE IN SOFTWARE
ANTENNA
C27 E1
BATTERY TERMINAL
muRata LQG15HS2N2B02D
PCM5102A
DISABLE NFC IN FIRMWARE
BUTTONS
ENCODER
Bourns SRR1005-100Y
J-LINK CONNECTOR
HEADERS
HEADPHONE JACK

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
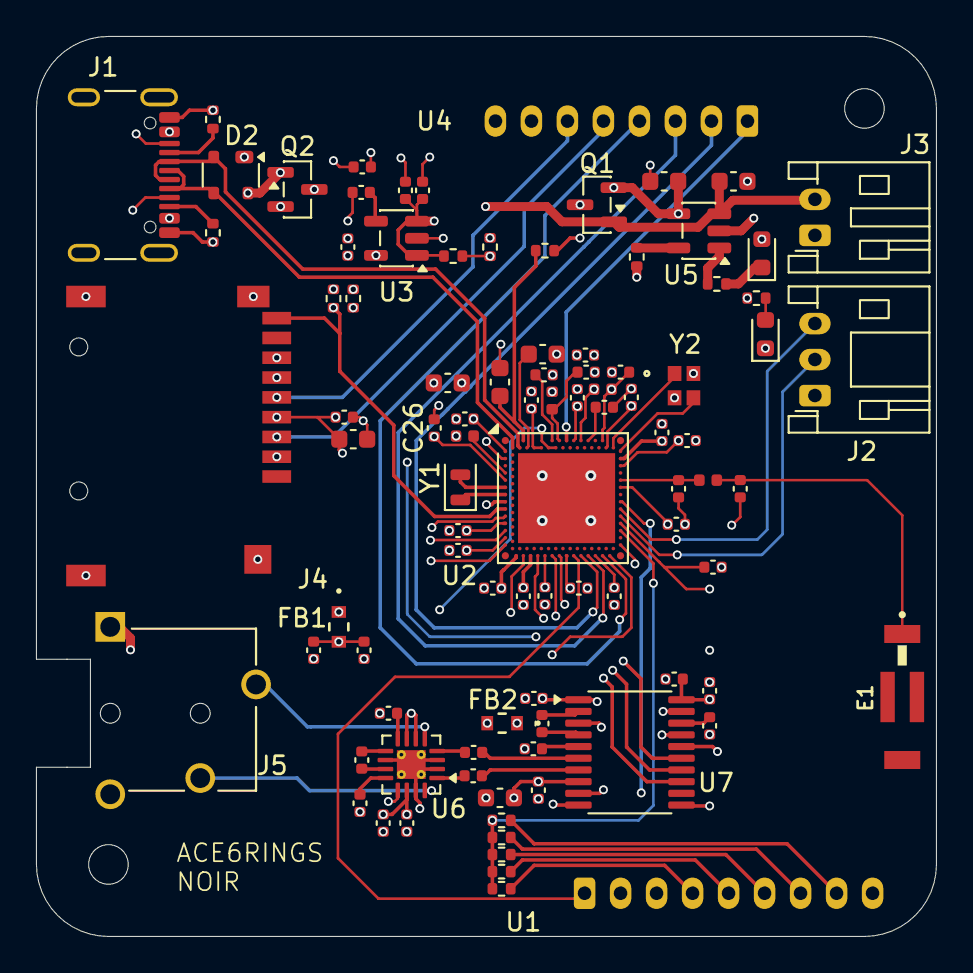
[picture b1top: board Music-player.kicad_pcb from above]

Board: 6 copper layers, 50.0 x 50.0 mm, 94 parts (1 on the bottom side), 68 nets.

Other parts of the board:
C9#2: 4.7u; C_0603_1608Metric

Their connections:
GND: C9#2.2; also elsewhere on the board

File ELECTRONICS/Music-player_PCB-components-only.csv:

Reference,Qty,Item,DNP,Exclude from BOM,Exclude from Board,Footprint,Datasheet,Link,Amount,Cost,SUBTOTAL,SHIPPING,TAXES,TOTAL
"C1,C4,C8,C10,C12,C24,C39,C40,C41,C43,C44,C45,C46,C50,C53",15,1u,,,,Capacitor_SMD:C_0402_1005Metric,,https://www.lcsc.com/product-detail/C29266.html?s_z=n_q_t_1u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,100,0.53,139.89,7.27,15.5729625,191.0429625
"C2, C26, C47",3,2.2u,,,,Capacitor_SMD:C_0402_1005Metric,,https://www.lcsc.com/product-detail/C170151.html?s_z=n_q_t_2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,50,0.5,,,,
"C3,C7,C15,C16,C17,C18,C19,C20,C21,C22,C23,C28,C29,C30,C31,C32,C33,C36,C38,C42,C48,C51,C52",23,100n,,,,Capacitor_SMD:C_0402_1005Metric,,https://www.lcsc.com/product-detail/C1525.html?s_z=n_q_t_100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,100,0.23,,,,
"C6,C9,C11,C27",4,4.7u,,,,Capacitor_SMD:C_0603_1608Metric,,https://www.lcsc.com/product-detail/C19666.html?s_z=n_q_t_4.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,10,0.22,,,,
C13,1,2.2n,,,,Capacitor_SMD:C_0402_1005Metric,,https://www.lcsc.com/product-detail/C107082.html?s_z=n_q_t_2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,100,0.42,,,,
C14,1,0.7p,,,,Capacitor_SMD:C_0402_1005Metric,,https://www.lcsc.com/product-detail/C161349.html?s_z=n_q_t_0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,50,0.83,,,,
"C37,C49",2,10u,,,,Capacitor_SMD:C_0603_1608Metric,,https://www.lcsc.com/product-detail/C96446.html?s_z=n_q_t_10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,20,1.07,,,,
C54,1,10n,,,,Capacitor_SMD:C_0402_1005Metric,,https://www.lcsc.com/product-detail/C15195.html?s_z=n_q_t_10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,100,0.25,,,,
C55,1,NC,DNP,,,Capacitor_SMD:C_0402_1005Metric,,,,,,,,
"D1, D3",2,POWER,,,,LED_SMD:LED_0603_1608Metric,,https://www.lcsc.com/product-detail/C19171394.html?s_z=n_q_t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,100,0.58,,,,
D2,1,PRTR5V0U2X,,,,Package_TO_SOT_SMD:SOT-143,https://assets.nexperia.com/documents/data-sheet/PRTR5V0U2X.pdf,https://www.lcsc.com/product-detail/C2827688.html?s_z=n_q_PR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,10,0.61,,,,
E1,1,2450AT43B100E,,,,MyFootprintLibrary:ANTENNA_2450AT43B100E,,https://www.lcsc.com/product-detail/C2917721.html?s_z=n_q_24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,1,0.77,,,,
"FB1,FB2",2,TDK MPZ1608S221ATA00,,,,myotherkicadfootprintlibrary:IND_1608_TDK,,https://www.lcsc.com/product-detail/C76815.html?s_z=n_q_TDK%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,10,0.15,,,,
J1,1,USB_C_Receptacle_USB2.0_16P,,,,Connector_USB:USB_C_Receptacle_GCT_USB4105-xx-A_16P_TopMnt_Horizontal,https://www.usb.org/sites/default/files/documents/usb_type-c.zip,https://www.lcsc.com/product-image/C5184243.html?whichImg=pc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,1,0.97,,,,
J2,1,JST CONNECTOR 1X3,,,,Connector_JST:JST_PH_S3B-PH-K_1x03_P2.00mm_Horizontal,,https://www.lcsc.com/product-detail/C157929.html?s_z=n_q_S3B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,10,0.49,,,,
J3,1,JST CONNECTOR 1X2,,,,Connector_JST:JST_PH_S2B-PH-K_1x02_P2.00mm_Horizontal,,https://www.lcsc.com/product-detail/C173752.html?s_z=n_q_S2B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,20,0.79,,,,
J4,1,MSD-4-A,,,,MyFootprintLibrary:CUI_MSD-4-A,,https://www.lcsc.com/product-detail/C22367949.html?s_z=n_q_m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,1,0.83,,,,
J5,1,SJ-43514,,,,MyFootprintLibrary:CUI_SJ-43514,,https://www.digikey.com/en/products/detail/same-sky-formerly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,1,1.34,,,,
"L1, L2, L3",3,10uH,,,,Inductor_SMD:L_0402_1005Metric,,https://www.lcsc.com/product-detail/C910650.html?s_z=n_q_10u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,5,3.01,,,,
L4,1,2.2n,,,,Inductor_SMD:L_0402_1005Metric,,https://www.lcsc.com/product-detail/C91240.html?s_z=n_q_2.2n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,10,0.5,,,,
"Q1,Q2",2,DMG2301L,,,,Package_TO_SOT_SMD:SOT-23,https://www.diodes.com/assets/Datasheets/DMG2301L.pdf,https://www.lcsc.com/product-detail/C7472914.html?s_z=n_q_DM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,10,0.58,,,,
"R1,R2",2,5.1K,,,,Resistor_SMD:R_0402_1005Metric,,https://www.lcsc.com/product-detail/C852856.html?s_z=n_q_t_5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,50,1.08,,,,
"R3, R13, R14",3,10k,,,,Resistor_SMD:R_0402_1005Metric,,https://www.lcsc.com/product-detail/C190095.html?s_z=n_q_t_1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,50,0.93,,,,
R4,1,2R2,,,,Resistor_SMD:R_0402_1005Metric,,https://www.lcsc.com/product-detail/C3013277.html?s_z=n_q_t_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,50,0.64,,,,
R5,1,100,,,,Resistor_SMD:R_0402_1005Metric,,https://www.lcsc.com/product-detail/C106232.html?s_z=n_q_t_1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,100,0.1,,,,
R6,1,1k,,,,Resistor_SMD:R_0402_1005Metric,,https://www.lcsc.com/product-detail/C852624.html?s_z=n_q_t_1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,50,0.89,,,,
R7,1,2.2k,,,,Resistor_SMD:R_0402_1005Metric,,https://www.lcsc.com/product-detail/C2906920.html?s_z=n_q_t_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,100,0.1,,,,
"R8,R9",2,1M,,,,Resistor_SMD:R_0402_1005Metric,,https://www.lcsc.com/product-detail/C2929915.html?s_z=n_q_2m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,100,0.1,,,,
R10,1,2k,,,,Resistor_SMD:R_0402_1005Metric,,https://www.lcsc.com/product-detail/C2906921.html?s_z=n_q_t_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,100,0.09,,,,
R11,1,22k,,,,Resistor_SMD:R_0402_1005Metric,,https://www.lcsc.com/product-detail/C82868.html?s_z=n_q_t_22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,100,0.1,,,,
R12,1,470,,,,Resistor_SMD:R_0402_1005Metric,,https://www.lcsc.com/product-detail/C2909361.html?s_z=n_q_t_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,100,0.1,,,,
R15,1,4.7k,,,,Resistor_SMD:R_0402_1005Metric,,https://www.lcsc.com/product-detail/C42396697.html?s_z=n_q_t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,100,0.22,,,,
SW1,1,B3U-1000P,,,,myotherkicadfootprintlibrary:B3U-1000P,,https://www.lcsc.com/product-detail/C231329.html?s_z=n_q_B3U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,5,0.89,,,,
U1,1,,,,,Connector_JST:JST_PH_S9B-PH-K_1x09_P2.00mm_Horizontal,,https://www.lcsc.com/product-detail/C157912.html?s_z=n_q_S9B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,5,0.92,,,,
U2,1,nRF5340-QKAA-R,,,,Package_DFN_QFN:Nordic_AQFN-94-1EP_7x7mm_P0.4mm,https://infocenter.nordicsemi.com/pdf/nRF5340_PS_v1.2.pdf,https://www.lcsc.com/product-detail/C3015611.html?s_z=n_q_nr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,1,7.59,,,,
U3,1,SPX3819M5-L-3-3,,,,Package_TO_SOT_SMD:SOT-23-5,https://www.exar.com/content/document.ashx?id=22106&language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,https://www.lcsc.com/product-detail/C9055.html?s_z=n_q_SPX38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,10,1.78,,,,
U4,1,,,,,Connector_JST:JST_PH_S8B-PH-K_1x08_P2.00mm_Horizontal,,https://www.lcsc.com/product-detail/C157915.html?s_z=n_q_JST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,5,0.54,,,,
U5,1,MCP73831-2-OT,,,,Package_TO_SOT_SMD:SOT-23-5,http://ww1.microchip.com/downloads/en/DeviceDoc/20001984g.pdf,https://www.lcsc.com/product-detail/C424093.html?s_z=s_p_x_M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,1,0.81,,,,
U6,1,TPA6132A2RTE,,,,Package_DFN_QFN:WQFN-16-1EP_3x3mm_P0.5mm_EP1.6x1.6mm_ThermalVias,https://www.ti.com/lit/ds/symlink/tpa6132a2.pdf,https://www.lcsc.com/product-detail/C69901.html?s_z=n_q_TPA6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,1,1.31,,,,
U7,1,PCM5102A,,,,Package_SO:TSSOP-20_4.4x6.5mm_P0.65mm,http://www.ti.com/lit/ds/symlink/pcm5100.pdf,https://www.lcsc.com/product-detail/C107671.html?s_z=n_q_%25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,1,1.11,,,,
Y1,1,Seiko SC-20S,,,,Crystal:Crystal_SMD_2012-2Pin_2.0x1.2mm,,https://www.digikey.com/en/products/detail/seiko-instruments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,1,0.72,,8.49,,
Y2,1,NX2016SA-CS06654,,,,myotherkicadfootprintlibrary:NX2016SA_NDK,,https://www.lcsc.com/product-detail/C5441424.html?s_z=n_q_p_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,1,0.44,,,,

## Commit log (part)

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2026-04-30 Add MIT License to the project
2026-04-30 Create Electronics
2026-05-16 First electronics iteration
2026-06-11 Create Code
2026-06-11 Create __
2026-06-13 Create wdq
2026-06-13 Create ws
2026-06-13 Create q2
2026-06-13 Create sq
2026-06-13 Create qdq
2026-06-13 Create E4WR3
2026-06-13 Create qq
2026-06-15 Create S
2026-06-18 Create settings
2026-06-18 Create R
2026-06-18 Create e
2026-06-18 Create c
2026-06-18 Create w
2026-06-18 Create d
2026-06-19 Binary
